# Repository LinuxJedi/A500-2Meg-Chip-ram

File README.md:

# Amiga 500/2000 2MB Chip RAM Mod

This is an adapter board to retrofit a 2MB Agnus into an Amiga 500/2000 and also includes 2MB of chip ram. It is based on [LIV2's design](https://github.com/LIV2/A500-2Meg-Chip-ram) but is easier to solder and has been remade in KiCad 6.

At present this particular design has only been tested on an Amiga 2000. It should, however, work on Amiga 500s as well, with the caveat that it might get in the way of the keyboard in the revision 5 Amiga 500 (if you try this please let me know).

**NOTE**: You need KiCad 5.99 or higher to be able to edit this project.

## Assembly Steps
1. Solder the DRAM, U4, U3
2. Solder the Capacitors & Resistor (Only fit VBB capacitor if your Agnus says VBB on the top!)
3. Solder the PLCC Socket making sure that the socket aligns exactly with the outline on the top of the PCB!
4. Prepare the pin headers by removing a pin from this corner of each as indicated here:<br/>

5. Solder the pin headers.
6. Solder a wire to A20 and connect the other end at one of the following locations:
   * Gary pin 36
   * CPU pin 48
   * JP5 Top left pad (Amiga 500 Rev 6)
7. Apply motherboard fixes required in the section below
8. Carefully desolder & remove the Agnus socket
9. Remove the same corner pin from each pin socket and solder them in replacing the agnus socket.
10. Insert the adapter

    **To make sure it is installed the correct way, pay attention to the marking of "1" on the PCB and on the Amiga they must match**

    On a Rev 6A Amiga 500 this means that the ram will be on the right hand side, on a Rev 5 it will be pointing downwards instead.

    Look from the sides to make sure the pins are going in to the headers.

    The following image is the installation in an Amiga 2000.

## Motherboard Fixes

### Amiga 500

Make sure that JP2 is set as shown:

### Amiga 2000

If you have 512KB of Chip RAM before installing the device you need to switch the position of J101, which is located near the power supply connector, to its opposite position.

You then need to remove J500, which is located near Gary. On some motherboard this will be a case of removing a jumper, some will be desoldering a bridge and some will require cutting a trace between the jumper pads.

## Jumper Settings
The default jumper settings do not need to be changed and will work on all systems. 

Rev 6A Amiga 500's have jumpers that can be used to provide the A20 signal on pin 35 instead of XCLK
This allows us to use this adapter without having to add the wire to A20 but note **this will mean you cannot use a genlock on this Amiga!**

In this case you must set J1 to 28M to bypass the XCLK/28M Mux then set J2 of the adapter to A20<br />
If you wish to do this then you will also need to change the jumper settings at J5 on your A500 motherboard

## Bill of materials

The components required are identical to LIV2's original design, but please be aware their locations have changed.

|Component|Location|QTY|Link|
|---------|--------|---|------|
|Ceramic Capacitor, 0.1uF, 0805|C1-6|6|[Mouser](https://www.mouser.com/ProductDetail/710-885012207098)|
|Ceramic Capacitor, 22pF, 0805|C7|1|[Mouser](https://www.mouser.com/ProductDetail/710-885012007053) |
|Resistor, 150 Ohm, 0805|R1|1|[Mouser](https://www.mouser.se/ProductDetail/652-CR0805JW-151ELF)|
|74AHC1G08 Single 2-Input AND Gate, SOT-23-5|U3|1|[Mouser](https://www.mouser.com/ProductDetail/595-SN74AHC1G08DBVR)|
|74AHCT158 Quad 2-input Multiplexer, SOIC-16|U4|1|[Mouser](https://www.mouser.com/ProductDetail/595-SN74AHCT158D) |
|PLCC-84 Socket, Through-hole|U2|1|[Mouser](https://www.mouser.com/ProductDetail/437-5408808424008) |
|5V, 1Mx16 EDO/FPM DRAM, SOJ-42<br>- K4F151611<br>- K4E151611<br>- GM71C18163C<br>- AS4C1M16E5|U5|1|eBay, Aliexpress etc|
|22-Pin, 2 Row Female header||4|[Mouser](https://www.mouser.se/ProductDetail/517-929975-01-11-RK)
|22-Pin, 2 Row Male header||4|[Mouser](https://www.mouser.se/ProductDetail/649-77313-118-22LF)

**Note**: Only solder C2 if the 8375 you are installing is marked with "VBB".

## PCBWay

I've made the PCBs available on PCBWay here: https://www.pcbway.com/project/member/?bmbno=0369642B-E3DA-48

## Sponsorship

If you like these projects and have built / sold a few yourself, please consider sponsoring. R&D for these projects isn't cheap and the sponsorship money goes into more designs for the future. Links for this are can be found in the "Sponsor" button at the top of the GitHub page for this project.

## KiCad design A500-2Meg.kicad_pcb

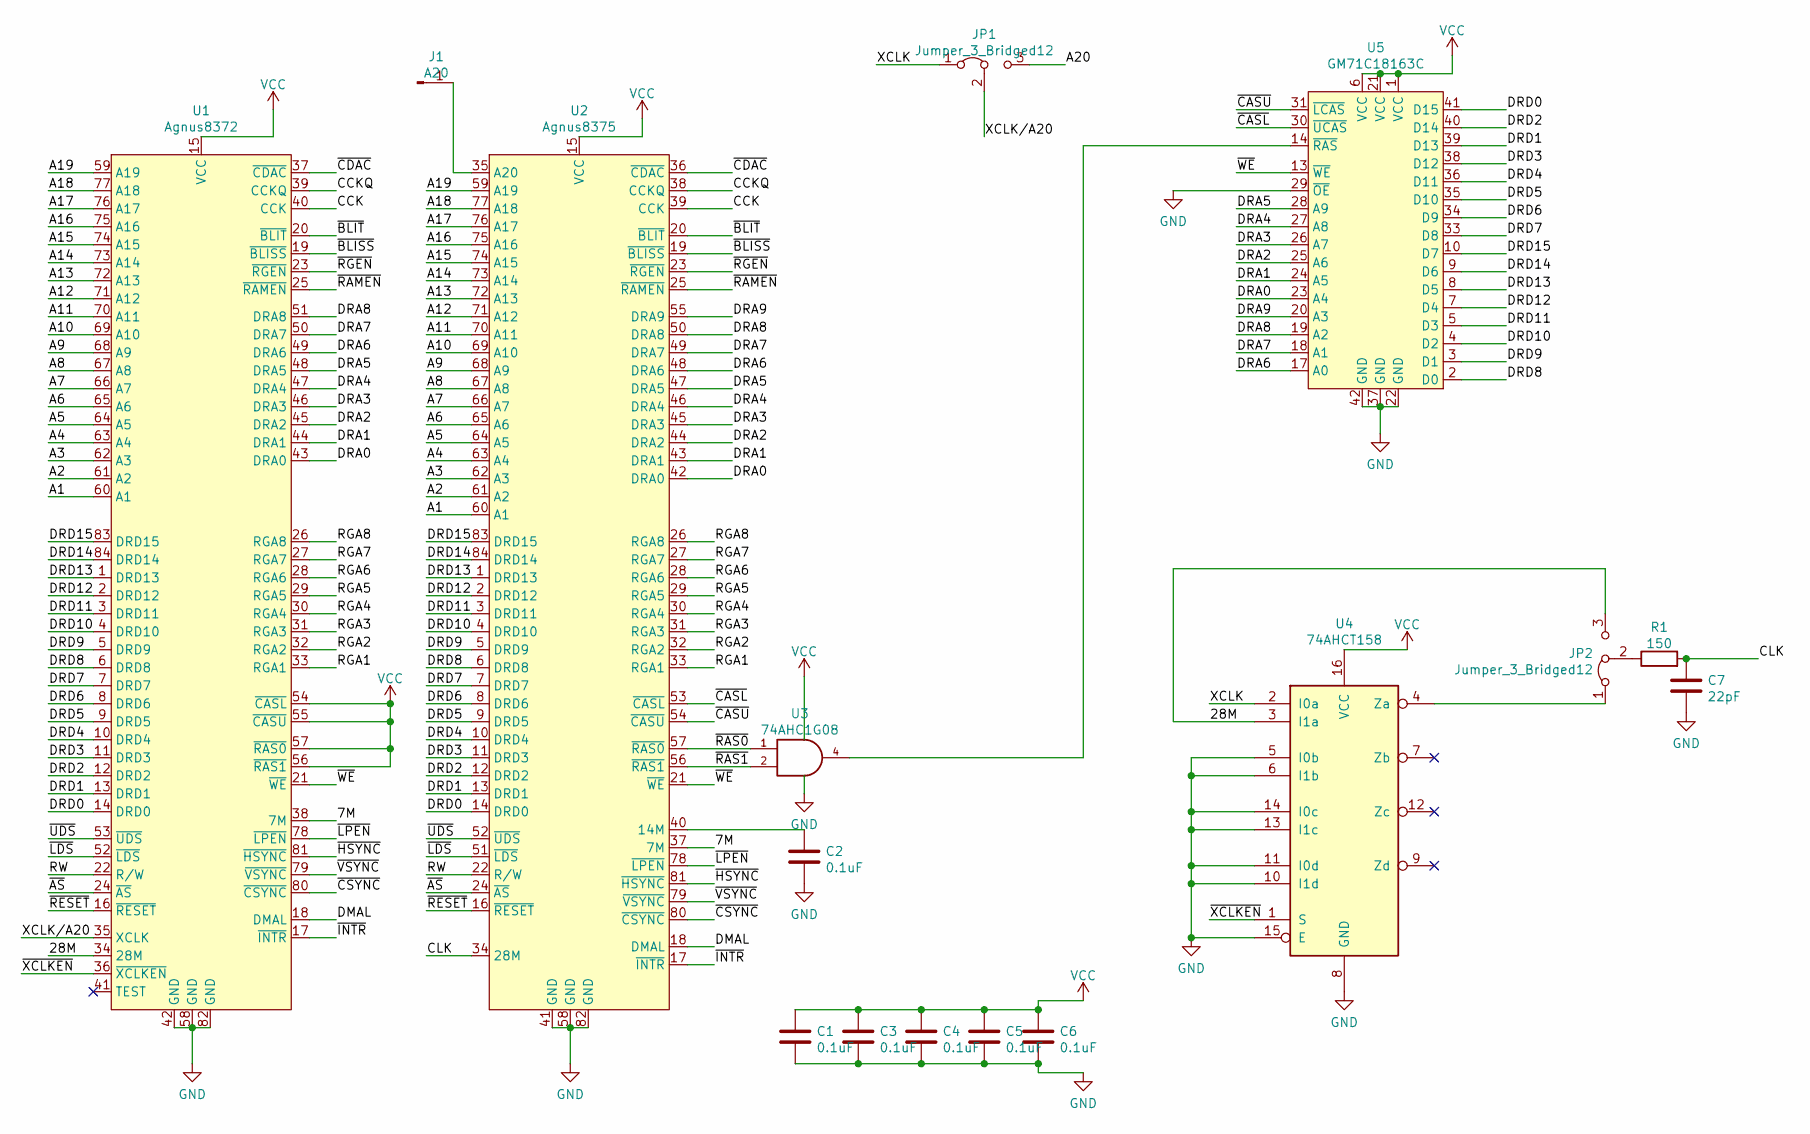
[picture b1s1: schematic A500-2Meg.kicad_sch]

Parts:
C1, C2, C3, C4, C5, C6: 0.1uF; C_0805_2012Metric_Pad1.18x1.45mm_HandSolder
C7: 22pF; C_0805_2012Metric_Pad1.18x1.45mm_HandSolder
J1: A20; PinHeader_1x01_P2.54mm_Vertical
JP1, JP2: Jumper_3_Bridged12; SolderJumper-3_P1.3mm_Bridged12_RoundedPad1.0x1.5mm
R1: 150; R_0805_2012Metric_Pad1.20x1.40mm_HandSolder
U1: Agnus8372; PLCC-84_THT-Socket
U2: Agnus8375; PLCC-84_THT-Socket
U3: 74AHC1G08; SOT-23-5_HandSoldering
U4: 74AHCT158; SOIC-16_3.9x9.9mm_P1.27mm
U5: GM71C18163C; SOJ-42

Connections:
/7M: U1.38 (7M), U2.37 (7M)
/28M: JP2.3 (B), U1.34 (28M), U4.3 (I1a)
/A1: U1.60 (A1), U2.60 (A1)
/A2: U1.61 (A2), U2.61 (A2)
/A3: U1.62 (A3), U2.62 (A3)
/A4: U1.63 (A4), U2.63 (A4)
/A5: U1.64 (A5), U2.64 (A5)
/A6: U1.65 (A6), U2.65 (A6)
/A7: U1.66 (A7), U2.66 (A7)
/A8: U1.67 (A8), U2.67 (A8)
/A9: U1.68 (A9), U2.68 (A9)
/A10: U1.69 (A10), U2.69 (A10)
/A11: U1.70 (A11), U2.70 (A11)
/A12: U1.71 (A12), U2.71 (A12)
/A13: U1.72 (A13), U2.72 (A13)
/A14: U1.73 (A14), U2.73 (A14)
/A15: U1.74 (A15), U2.74 (A15)
/A16: U1.75 (A16), U2.75 (A16)
/A17: U1.76 (A17), U2.76 (A17)
/A18: U1.77 (A18), U2.77 (A18)
/A19: U1.59 (A19), U2.59 (A19)
/A20: JP1.3 (B)
/CCK: U1.40 (CCK), U2.39 (CCK)
/CCKQ: U1.39 (CCKQ), U2.38 (CCKQ)
/CLK: C7.1, R1.2, U2.34 (28M)
/DMAL: U1.18 (DMAL), U2.18 (DMAL)
/DRA0: U1.43 (DRA0), U2.42 (DRA0), U5.23 (A4)
/DRA1: U1.44 (DRA1), U2.43 (DRA1), U5.24 (A5)
/DRA2: U1.45 (DRA2), U2.44 (DRA2), U5.25 (A6)
/DRA3: U1.46 (DRA3), U2.45 (DRA3), U5.26 (A7)
/DRA4: U1.47 (DRA4), U2.46 (DRA4), U5.27 (A8)
/DRA5: U1.48 (DRA5), U2.47 (DRA5), U5.28 (A9)
/DRA6: U1.49 (DRA6), U2.48 (DRA6), U5.17 (A0)
/DRA7: U1.50 (DRA7), U2.49 (DRA7), U5.18 (A1)
/DRA8: U1.51 (DRA8), U2.50 (DRA8), U5.19 (A2)
/DRA9: U2.55 (DRA9), U5.20 (A3)
/DRD0: U1.14 (DRD0), U2.14 (DRD0), U5.41 (D15)
/DRD1: U1.13 (DRD1), U2.13 (DRD1), U5.39 (D13)
/DRD2: U1.12 (DRD2), U2.12 (DRD2), U5.40 (D14)
/DRD3: U1.11 (DRD3), U2.11 (DRD3), U5.38 (D12)
/DRD4: U1.10 (DRD4), U2.10 (DRD4), U5.36 (D11)
/DRD5: U1.9 (DRD5), U2.9 (DRD5), U5.35 (D10)
/DRD6: U1.8 (DRD6), U2.8 (DRD6), U5.34 (D9)
/DRD7: U1.7 (DRD7), U2.7 (DRD7), U5.33 (D8)
/DRD8: U1.6 (DRD8), U2.6 (DRD8), U5.2 (D0)
/DRD9: U1.5 (DRD9), U2.5 (DRD9), U5.3 (D1)
/DRD10: U1.4 (DRD10), U2.4 (DRD10), U5.4 (D2)
/DRD11: U1.3 (DRD11), U2.3 (DRD11), U5.5 (D3)
/DRD12: U1.2 (DRD12), U2.2 (DRD12), U5.7 (D4)
/DRD13: U1.1 (DRD13), U2.1 (DRD13), U5.8 (D5)
/DRD14: U1.84 (DRD14), U2.84 (DRD14), U5.9 (D6)
/DRD15: U1.83 (DRD15), U2.83 (DRD15), U5.10 (D7)
/RGA1: U1.33 (RGA1), U2.33 (RGA1)
/RGA2: U1.32 (RGA2), U2.32 (RGA2)
/RGA3: U1.31 (RGA3), U2.31 (RGA3)
/RGA4: U1.30 (RGA4), U2.30 (RGA4)
/RGA5: U1.29 (RGA5), U2.29 (RGA5)
/RGA6: U1.28 (RGA6), U2.28 (RGA6)
/RGA7: U1.27 (RGA7), U2.27 (RGA7)
/RGA8: U1.26 (RGA8), U2.26 (RGA8)
/RW: U1.22 (R/W), U2.22 (R/W)
/XCLK: JP1.1 (A), U4.2 (I0a)
/XCLK/A20: JP1.2 (C), U1.35 (XCLK)
/~AS: U1.24 (~AS), U2.24 (~AS)
/~BLISS: U1.19 (~BLISS), U2.19 (~BLISS)
/~BLIT: U1.20 (~BLIT), U2.20 (~BLIT)
/~CASL: U2.53 (~CASL), U5.30 (~UCAS)
/~CASU: U2.54 (~CASU), U5.31 (~LCAS)
/~CDAC: U1.37 (~CDAC), U2.36 (~CDAC)
/~CSYNC: U1.80 (~CSYNC), U2.80 (~CSYNC)
/~HSYNC: U1.81 (~HSYNC), U2.81 (~HSYNC)
/~INTR: U1.17 (~INTR), U2.17 (~INTR)
/~LDS: U1.52 (~LDS), U2.51 (~LDS)
/~LPEN: U1.78 (~LPEN), U2.78 (~LPEN)
/~RAMEN: U1.25 (~RAMEN), U2.25 (~RAMEN)
/~RAS0: U2.57 (~RAS0), U3.1
/~RAS1: U2.56 (~RAS1), U3.2
/~RESET: U1.16 (~RESET), U2.16 (~RESET)
/~RGEN: U1.23 (~RGEN), U2.23 (~RGEN)
/~UDS: U1.53 (~UDS), U2.52 (~UDS)
/~VSYNC: U1.79 (~VSYNC), U2.79 (~VSYNC)
/~WE: U1.21 (~WE), U2.21 (~WE), U5.13 (~WE)
/~XCLKEN: U1.36 (~XCLKEN), U4.1 (S)
GND: C1.2, C2.2, C3.2, C4.2, C5.2, C6.2, C7.2, U1.42 (GND), U1.58 (GND), U1.82 (GND), U2.41 (GND), U2.58 (GND), U2.82 (GND), U3.3 (GND), U4.5 (I0b), U4.6 (I1b), U4.8 (GND), U4.10 (I1d), U4.11 (I0d), U4.13 (I1c), U4.14 (I0c), U4.15 (E), U5.22 (GND), U5.29 (~OE), U5.37 (GND), U5.42 (GND)
unnamed: C2.1, U2.40 (14M)
unnamed: J1.1, U2.35 (A20)
unnamed: JP2.1 (A), U4.4 (Za)
unnamed: JP2.2 (C), R1.1
unnamed: U3.4, U5.14 (~RAS)
VCC: C1.1, C3.1, C4.1, C5.1, C6.1, U1.15 (VCC), U1.54 (~CASL), U1.55 (~CASU), U1.56 (~RAS1), U1.57 (~RAS0), U2.15 (VCC), U3.5 (VCC), U4.16 (VCC), U5.1 (VCC), U5.6 (VCC), U5.21 (VCC)

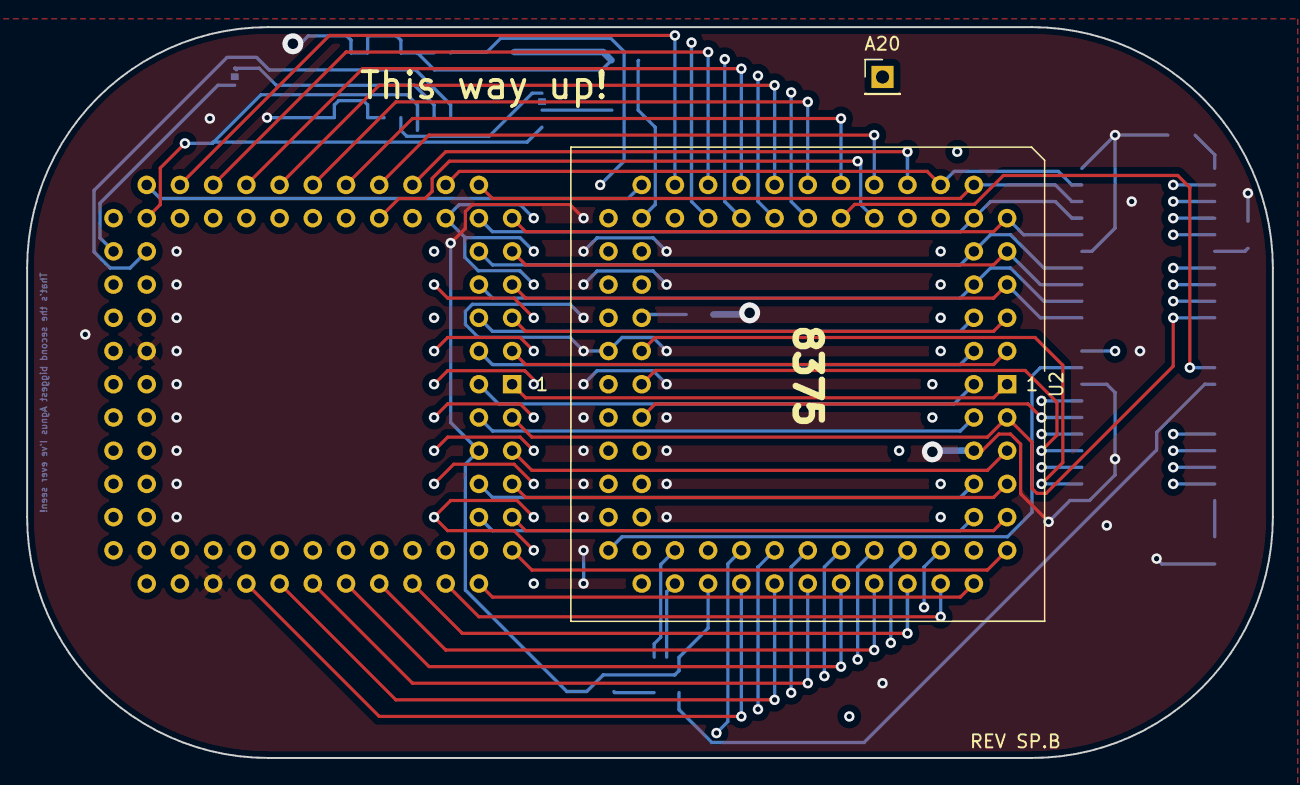
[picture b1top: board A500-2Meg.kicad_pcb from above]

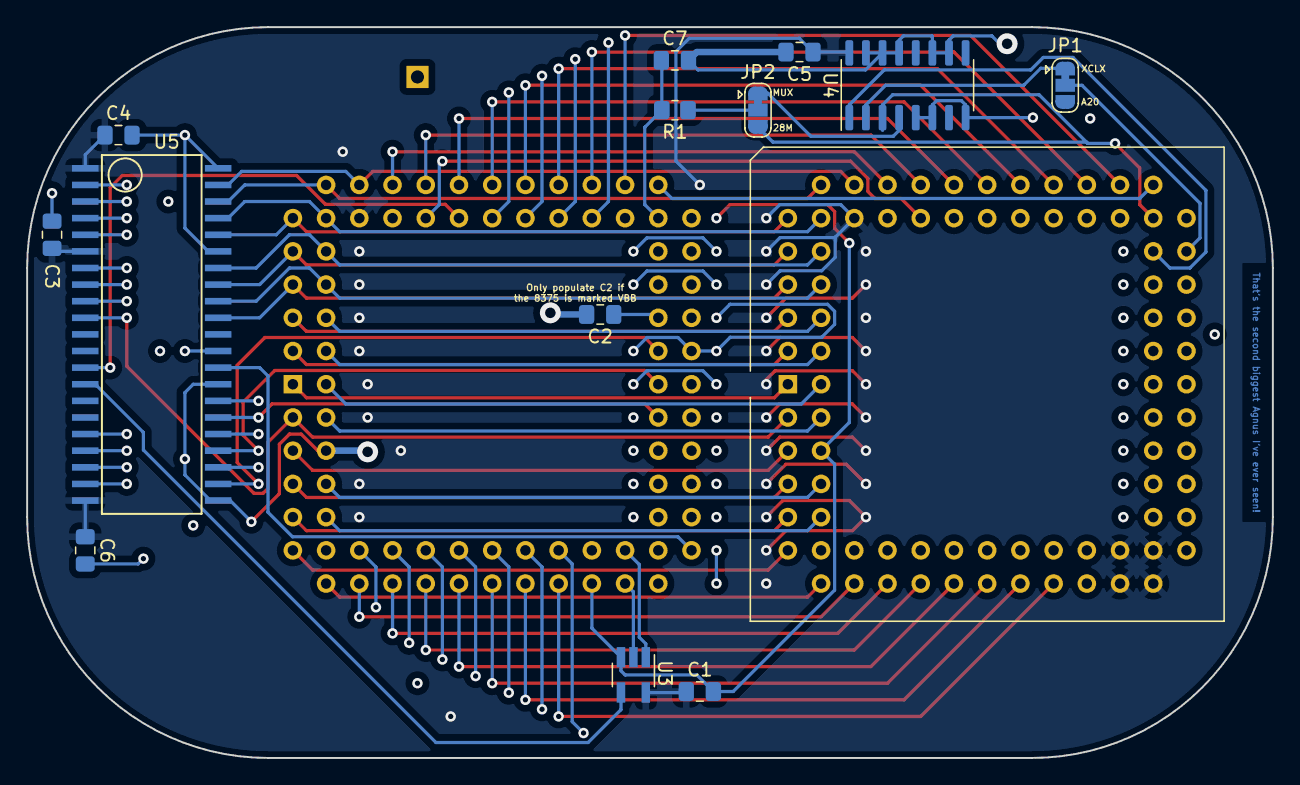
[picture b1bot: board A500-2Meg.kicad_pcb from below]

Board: 4 copper layers, 95.3 x 55.9 mm, 16 parts (13 on the bottom side), 89 nets.

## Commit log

2021-06-10 LinuxJedi version of the adaptor
    Completely remade in KiCad 5.99. Designed to be easier to solder.
2021-06-10 Fix BOM
2021-06-10 README updates
2021-06-11 Cleanups and make more PCB manufacturer friendly
